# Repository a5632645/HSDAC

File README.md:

# CH32V305-UAC2
ch32v305fbp6 + es9018k2m + opa1678 usb dac  
> [!NOTE]
> Due to using inexpensive components, the clock has approximately a 200 Hz error. Additionally, the MCLK GPIO speed exceeds the maximum 50 MHz limit at 192 kHz.
> If desired, you can use an external crystal for the I2S MCLK clock.

> [!NOTE]
> this dac only support 48k,96k,192k 32bits, dsd and other formats are not considered

> [!NOTE]
> This DAC only supports high-speed connections, so do not connect it through a USB hub.
> Any clicks that occur are a result of the computer not sending data within a given time. Therefore, you may hear clicks during periods of high system load.
# IMAGE

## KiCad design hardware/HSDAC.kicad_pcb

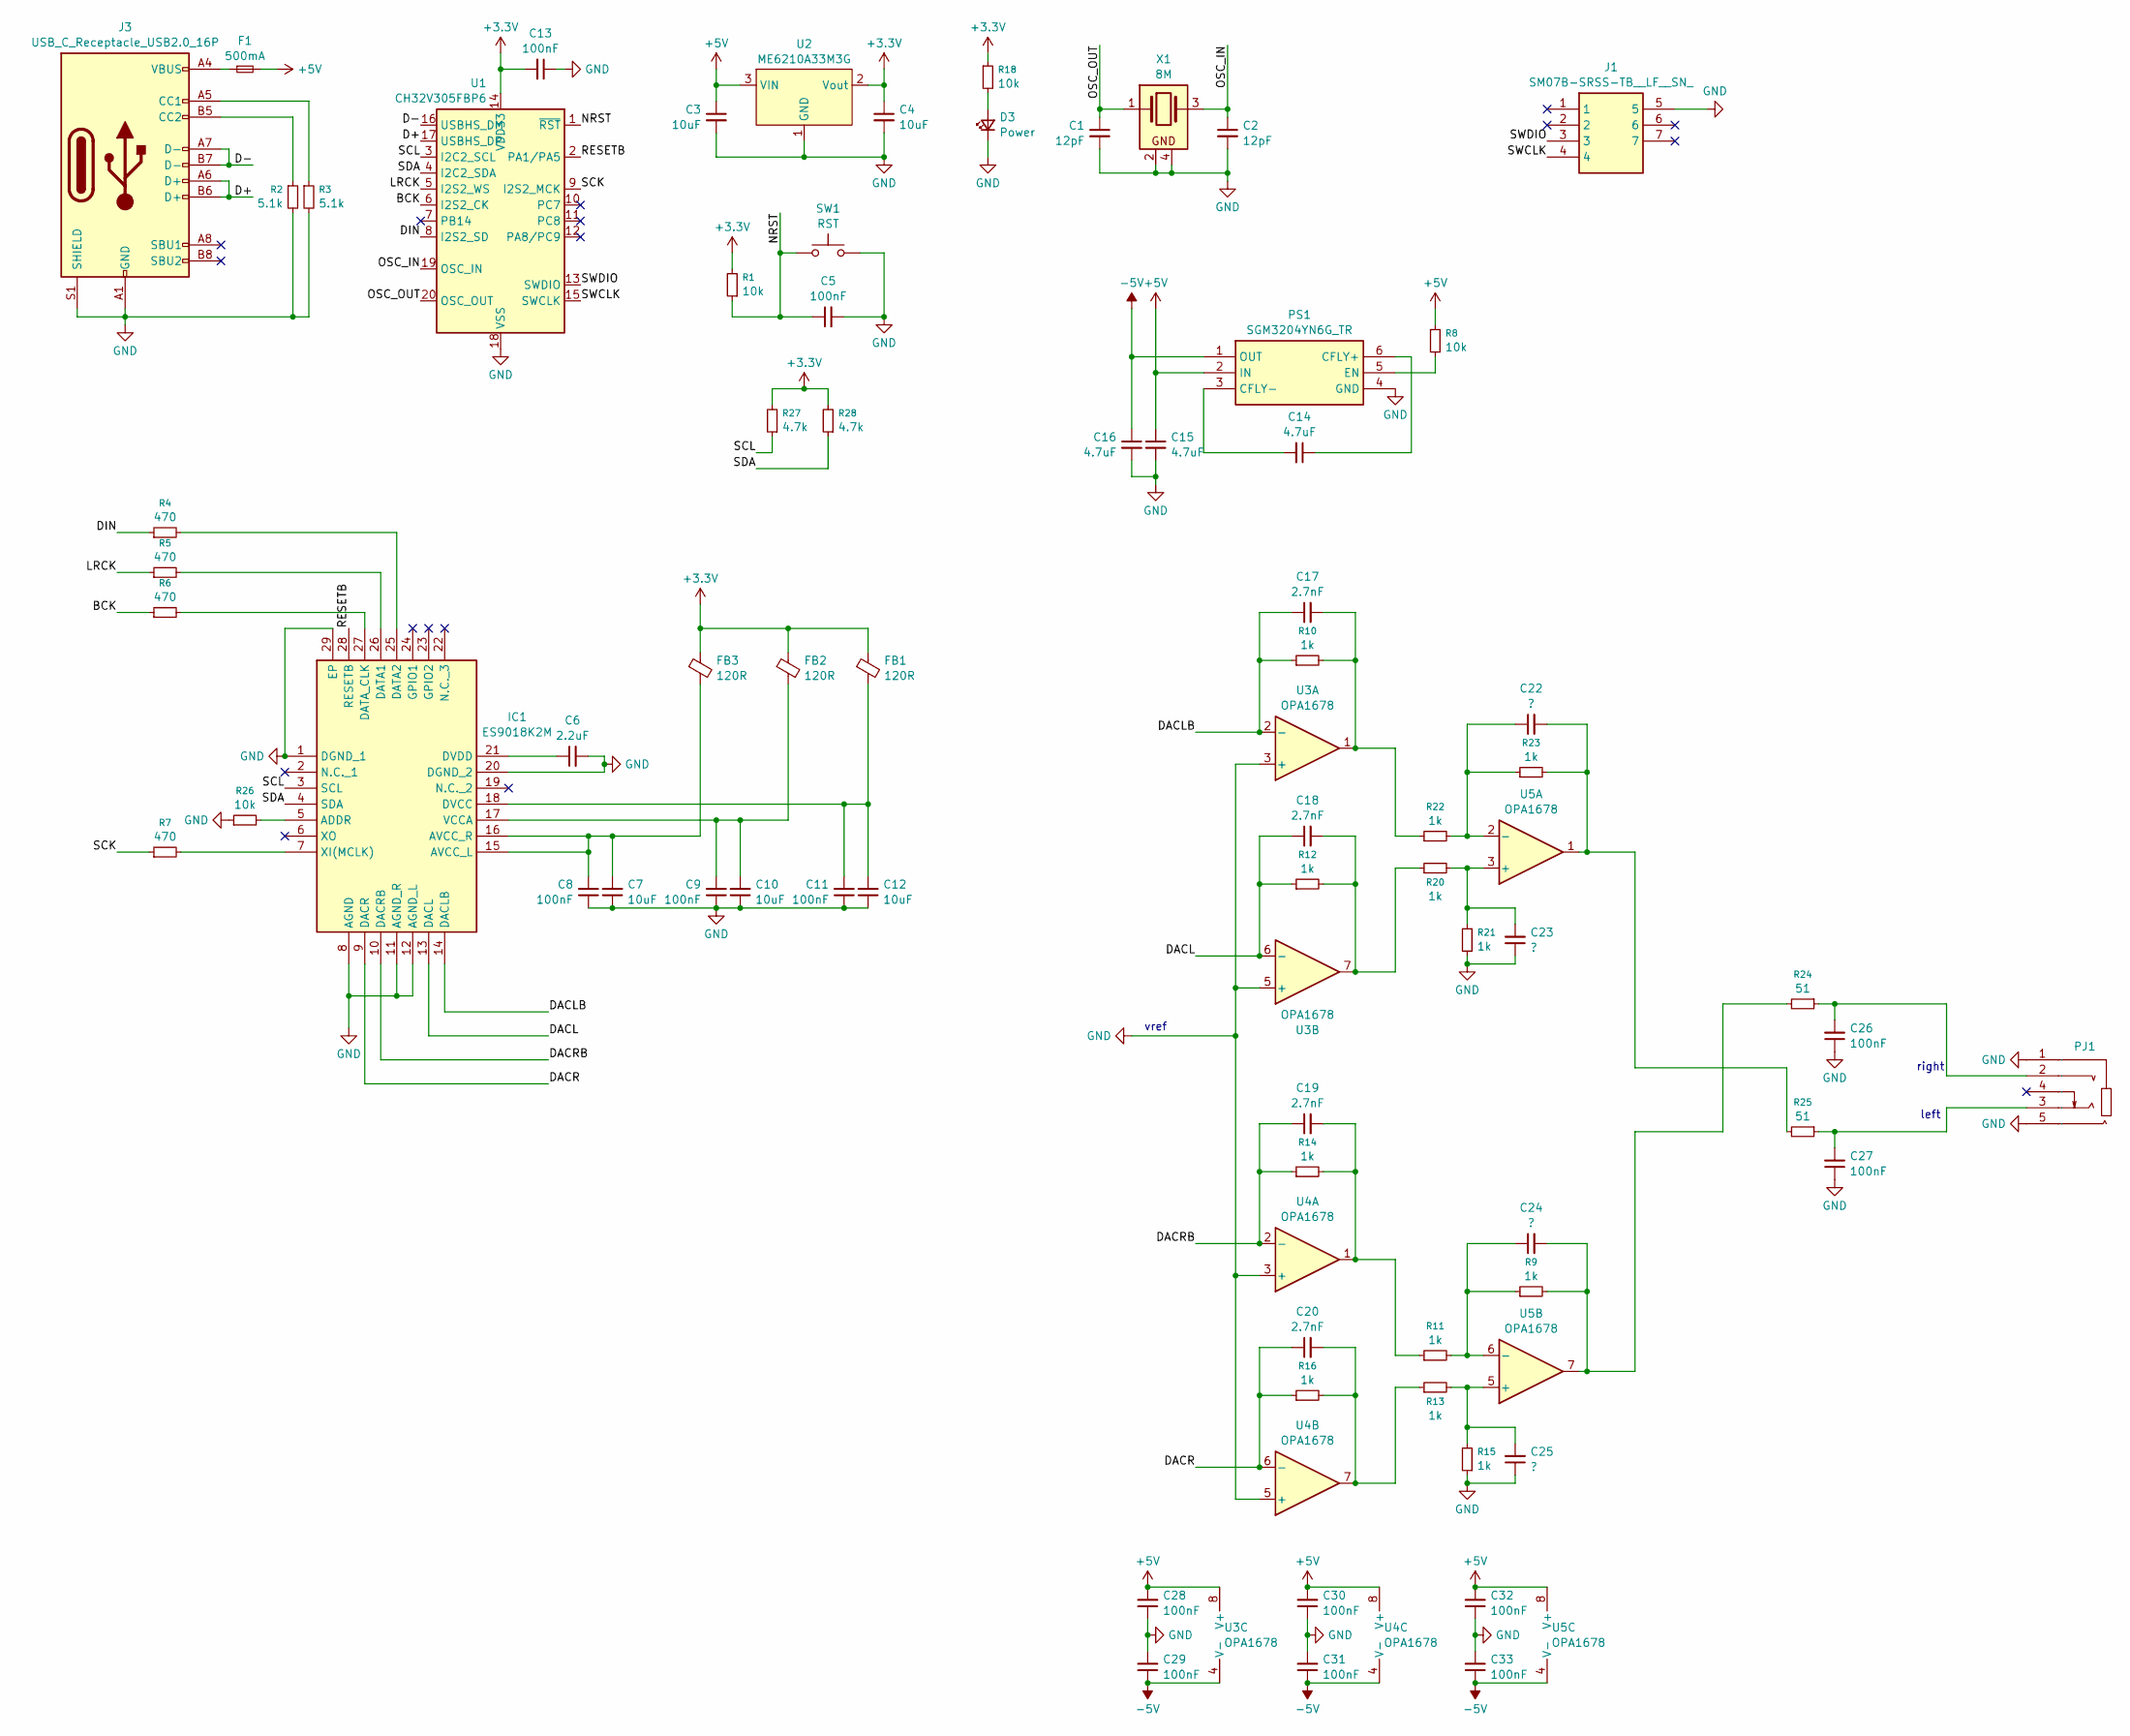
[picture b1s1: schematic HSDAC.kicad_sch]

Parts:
C1, C2: 12pF; C_0603_1608Metric_Pad1.05x0.95mm_HandSolder
C3, C4, C7, C10, C12: 10uF; C_0603_1608Metric_Pad1.05x0.95mm_HandSolder
C5, C8, C9, C11, C13, C26, C27, C28, C29, C30, C31, C32, C33: 100nF; C_0603_1608Metric_Pad1.05x0.95mm_HandSolder
C6: 2.2uF; C_0603_1608Metric_Pad1.05x0.95mm_HandSolder
C14, C15, C16: 4.7uF; C_0603_1608Metric_Pad1.05x0.95mm_HandSolder
C17, C18, C19, C20: 2.7nF; C_0603_1608Metric_Pad1.05x0.95mm_HandSolder
C22, C23, C24, C25: ?; C_0603_1608Metric_Pad1.05x0.95mm_HandSolder
D3: Power; LED_0805_2012Metric
F1: 500mA; Fuse_0603_1608Metric
FB1, FB2, FB3: 120R; Ferrite_0603_1608Metric
IC1: ES9018K2M; QFN50P500X500X90-29N-D; Manufacturer_Part_Number ES9018K2M; Mouser Part Number 460-ES9018K2M
J1: SM07B-SRSS-TB__LF__SN_; SM07B-SRSS-TB; Manufacturer_Part_Number SM07B-SRSS-TB (LF)(SN)
J3: USB_C_Receptacle_USB2.0_16P; USB_C_Receptacle_G-Switch_GT-USB-7010ASV
PJ1: AUDIO-IN-SMD_PJ-327A_C22355751; Manufacturer Part PJ-327A; LCSC Part Name PJ-327A
PS1: SGM3204YN6G_TR; SOT95P280X125-6N; Manufacturer_Part_Number SGM3204YN6G/TR
R1, R8, R18, R26: 10k; R_0603_1608Metric_Pad0.98x0.95mm_HandSolder
R2, R3: 5.1k; R_0603_1608Metric_Pad0.98x0.95mm_HandSolder
R4, R5, R6, R7: 470; R_0603_1608Metric_Pad0.98x0.95mm_HandSolder
R9, R10, R11, R12, R13, R14, R15, R16, R20, R21, R22, R23: 1k; R_0603_1608Metric_Pad0.98x0.95mm_HandSolder
R24, R25: 51; R_0603_1608Metric_Pad0.98x0.95mm_HandSolder
R27, R28: 4.7k; R_0603_1608Metric_Pad0.98x0.95mm_HandSolder
SW1: RST; SW-SMD_L4.0-W3.0-LS4.8-1
U1: CH32V305FBP6; TSSOP-20_4.4x6.5mm_P0.65mm
U2: ME6210A33M3G; SOT-23
U3, U4, U5: OPA1678; SOIC-8_3.9x4.9mm_P1.27mm
X1: 8M; Crystal_SMD_3225-4Pin_3.2x2.5mm

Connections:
+3.3V: C4.1, C13.2, FB1.1, FB2.1, FB3.1, R1.2, R18.1, R27.2, R28.2, U1.14 (VDD33), U2.2 (Vout)
+5V: C3.1, C15.1, C28.2, C30.2, C32.2, F1.2, PS1.2 (IN), R8.2, U2.3 (VIN), U3.8 (V+), U4.8 (V+), U5.8 (V+)
-5V: C16.1, C29.1, C31.1, C33.1, PS1.1 (OUT), U3.4 (V-), U4.4 (V-), U5.4 (V-)
/BCK: R6.1, U1.6 (I2S2_CK)
/D+: J3.A6 (D+), J3.B6 (D+), U1.17 (USBHS_DP)
/D-: J3.A7 (D-), J3.B7 (D-), U1.16 (USBHS_DM)
/DACL: C18.1, IC1.13 (DACL), R12.1, U3.6 (-)
/DACLB: C17.1, IC1.14 (DACLB), R10.1, U3.2 (-)
/DACR: C20.1, IC1.9 (DACR), R16.1, U4.6 (-)
/DACRB: C19.1, IC1.10 (DACRB), R14.1, U4.2 (-)
/DIN: R4.1, U1.8 (I2S2_SD)
/LRCK: R5.1, U1.5 (I2S2_WS)
/NRST: C5.1, R1.1, SW1.1, U1.1 (~RST)
/OSC_IN: C2.1, U1.19 (OSC_IN), X1.3
/OSC_OUT: C1.1, U1.20 (OSC_OUT), X1.1
/RESETB: IC1.28 (RESETB), U1.2 (PA1/PA5)
/SCK: R7.1, U1.9 (I2S2_MCK)
/SCL: IC1.3 (SCL), R27.1, U1.3 (I2C2_SCL)
/SDA: IC1.4 (SDA), R28.1, U1.4 (I2C2_SDA)
/SWCLK: J1.4, U1.15 (SWCLK)
/SWDIO: J1.3, U1.13 (SWDIO)
GND: C1.2, C2.2, C3.2, C4.2, C5.2, C6.2, C7.1, C8.1, C9.1, C10.1, C11.1, C12.1, C13.1, C15.2, C16.2, C23.1, C25.1, C26.1, C27.1, C28.1, C29.2, C30.1, C31.2, C32.1, C33.2, D3.1 (K), IC1.1 (DGND_1), IC1.8 (AGND), IC1.11 (AGND_R), IC1.12 (AGND_L), IC1.20 (DGND_2), IC1.29 (EP), J1.5, J3.A1 (GND), J3.A12 (GND), J3.B1 (GND), J3.B12 (GND), J3.S1 (SHIELD), PJ1.1, PJ1.5, PS1.4 (GND), R2.2, R3.2, R15.1, R21.1, R26.1, SW1.2, U1.18 (VSS), U2.1 (GND), U3.3 (+), U3.5 (+), U4.3 (+), U4.5 (+), X1.2, X1.4
unnamed: C17.2, R10.2, R22.1, U3.1
unnamed: C18.2, R12.2, R20.1, U3.7
unnamed: C19.2, R11.1, R14.2, U4.1
unnamed: C20.2, R13.1, R16.2, U4.7
unnamed: C22.2, R23.2, R25.2, U5.1
unnamed: C24.2, R9.2, R24.2, U5.7
unnamed: C26.2, PJ1.2, R24.1
unnamed: C27.2, PJ1.3, R25.1
unnamed: D3.2 (A), R18.2
unnamed: F1.1, J3.A4 (VBUS), J3.A9 (VBUS), J3.B4 (VBUS), J3.B9 (VBUS)
unnamed: IC1.5 (ADDR), R26.2
unnamed: C7.2, C8.2, FB3.2, IC1.15 (AVCC_L), IC1.16 (AVCC_R)
unnamed: IC1.26 (DATA1), R5.2
unnamed: IC1.25 (DATA2), R4.2
unnamed: IC1.27 (DATA_CLK), R6.2
unnamed: C11.2, C12.2, FB1.2, IC1.18 (DVCC)
unnamed: C6.1, IC1.21 (DVDD)
unnamed: C9.2, C10.2, FB2.2, IC1.17 (VCCA)
unnamed: IC1.7 (XI(MCLK)), R7.2
unnamed: J3.A5 (CC1), R3.1
unnamed: J3.B5 (CC2), R2.1
unnamed: C14.1, PS1.6 (CFLY+)
unnamed: C14.2, PS1.3 (CFLY-)
unnamed: PS1.5 (EN), R8.1
unnamed: C23.2, R20.2, R21.2, U5.3 (+)
unnamed: C22.1, R22.2, R23.1, U5.2 (-)
unnamed: C25.2, R13.2, R15.2, U5.5 (+)
unnamed: C24.1, R9.1, R11.2, U5.6 (-)

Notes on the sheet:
right
left
vref

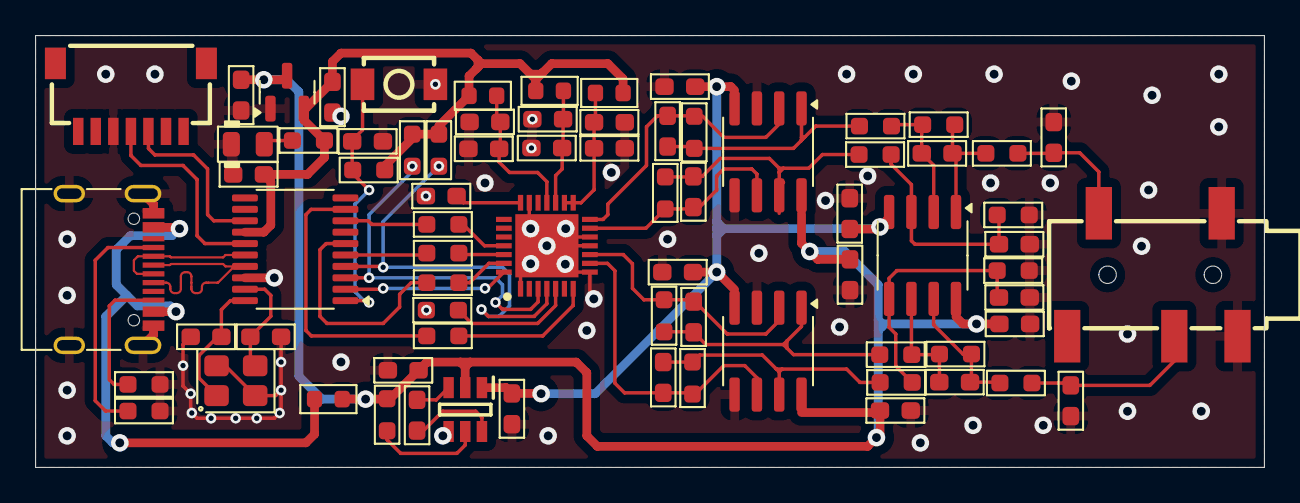
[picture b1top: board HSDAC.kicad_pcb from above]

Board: 2 copper layers, 70.0 x 24.6 mm, 75 parts (0 on the bottom side), 50 nets.

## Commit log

2025-05-24 init
2025-05-24 readme
2025-05-24 usb cdc!理解了一些usb但还是不够熟练（；´д｀）ゞ
2025-05-27 uac2.0!
2025-05-29 集成了CDC调试，必须修好自适应采样率
2025-05-30 uac!至少能跑了?
2025-05-31 why反馈端点也不行
2025-05-31 非常好时钟，使我偏差+-300hz，可惜反馈端点太监了不对
2025-06-01 你说得对，但是我的USB声卡没有反馈端点，感觉不如elipitic blep重采样
2025-06-02 perfect 48k!
2025-06-02 perfect 48k&96k,192k虽然显示一直溢出但声音也是连续的？
2025-06-02 what the hell is the bug from!
2025-06-02 what the hell is the bug come from 2? fuck windows usb
2025-06-03 fix bugs
2025-06-03 感觉不如重采样通用...
2025-06-03 no, jitterh和反馈明显更好好吧
2025-06-03 我在不HIFI和眼力挑战中获得了0分的成绩，你也来试试吧
2025-06-04 总线速度不够？改为3倍频了，MCLK到GPIO引脚上限也能工作？
2025-06-04 更新 README.md
2025-06-13 修复声道和运放封装错误
2025-06-14 omg,我合并错了
2025-06-15 add image
2025-06-16 hid通信队列成功
2025-06-18 添加了HID bootloader
2025-06-19 sick
2025-06-27 barely can use
2025-06-29 add latency control
2025-07-01 shorten the buffer size
2025-07-01 more short
2025-07-01 SCK的电阻和实际不一样
